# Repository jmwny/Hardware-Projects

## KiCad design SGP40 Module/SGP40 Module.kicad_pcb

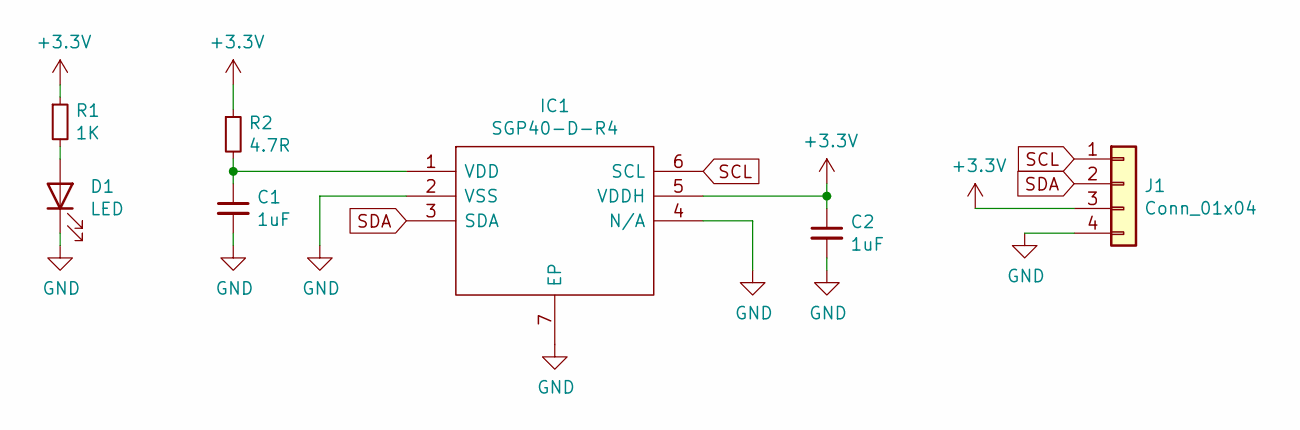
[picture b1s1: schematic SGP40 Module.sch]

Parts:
C1, C2: 1uF; C_0805_2012Metric
D1: LED; LED_0805_2012Metric
IC1: SGP40-D-R4; SON80P244X244X95-7N; Mouser Part Number 403-SGP40-D-R4
J1: Conn_01x04; PinHeader_1x04_P2.54mm_Vertical
R1: 1K; R_0805_2012Metric
R2: 4.7R; R_0805_2012Metric

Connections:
+3V3: C2.1, IC1.5 (VDDH), J1.3, R1.1, R2.1
GND: C1.2, C2.2, D1.1 (K), IC1.2 (VSS), IC1.4 (N/A), IC1.7 (EP), J1.4
unnamed: C1.1, IC1.1 (VDD), R2.2
unnamed: D1.2 (A), R1.2
SCL: IC1.6 (SCL), J1.1
SDA: IC1.3 (SDA), J1.2

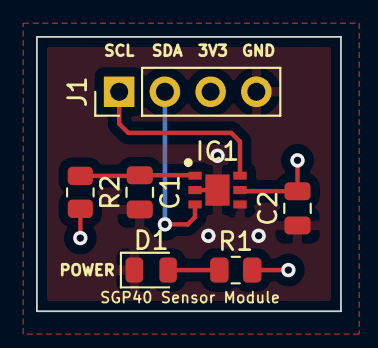
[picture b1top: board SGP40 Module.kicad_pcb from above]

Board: 4 copper layers, 16.9 x 15.2 mm, 7 parts (0 on the bottom side), 6 nets.

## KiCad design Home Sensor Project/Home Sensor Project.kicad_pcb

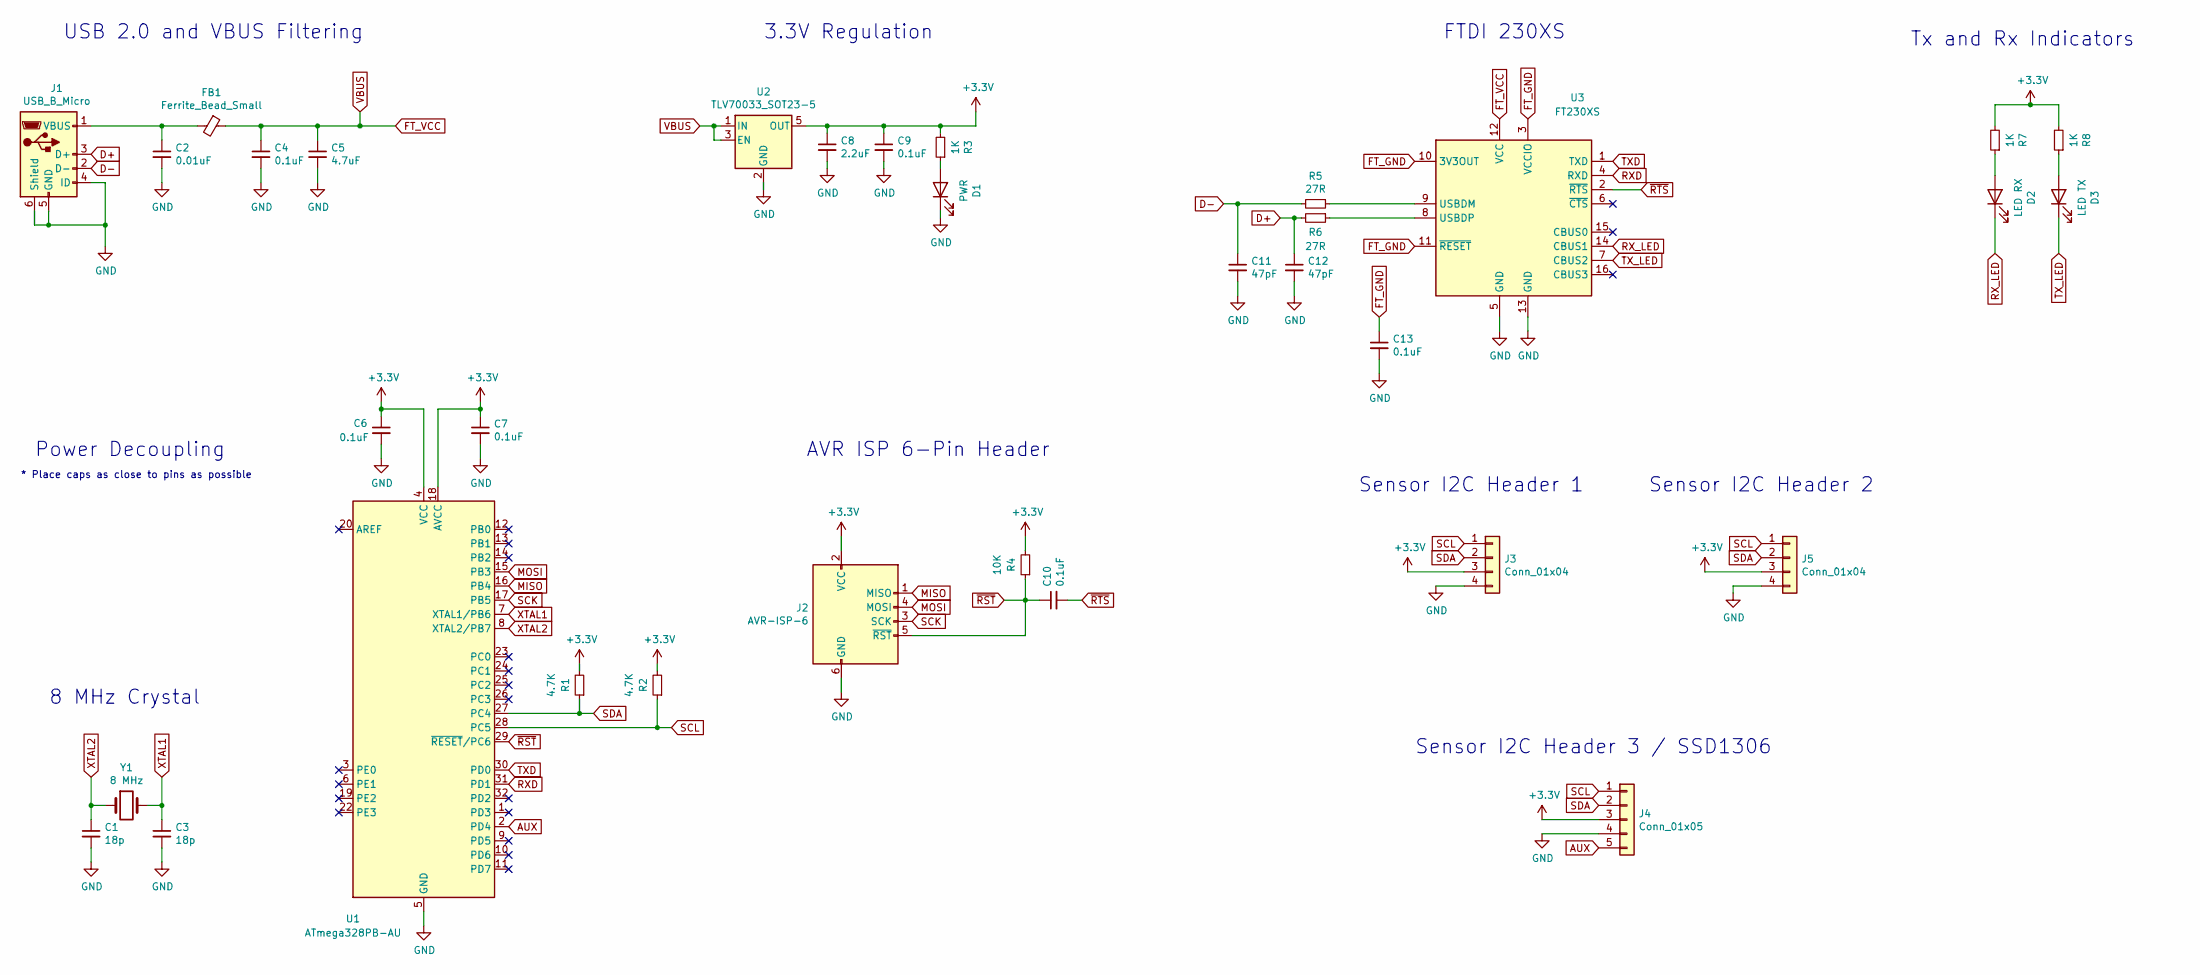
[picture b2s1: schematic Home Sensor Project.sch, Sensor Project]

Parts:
C1, C3: 18p; C_0805_2012Metric
C2: 0.01uF; C_0805_2012Metric
C4, C6, C7, C9, C10, C13: 0.1uF; C_0805_2012Metric
C5: 4.7uF; C_0805_2012Metric
C8: 2.2uF; C_0805_2012Metric
C11, C12: 47pF; C_0603_1608Metric
D1: PWR; LED_0805_2012Metric
D2: LED RX; LED_0805_2012Metric
D3: LED TX; LED_0805_2012Metric
FB1: Ferrite_Bead_Small; L_0805_2012Metric
J1: USB_B_Micro; USB_Micro-B_Amphenol_10118194_Horizontal
J2: AVR-ISP-6; PinHeader_2x03_P2.54mm_Vertical
J3, J5: Conn_01x04; PinHeader_1x04_P2.54mm_Vertical
J4: Conn_01x05; PinHeader_1x05_P2.54mm_Vertical
R1, R2: 4.7K; R_0805_2012Metric
R3, R7, R8: 1K; R_0805_2012Metric
R4: 10K; R_0805_2012Metric
R5, R6: 27R; R_0603_1608Metric
U1: ATmega328PB-AU; TQFP-32_7x7mm_P0.8mm
U2: TLV70033_SOT23-5; SOT-23-5
U3: FT230XS; SSOP-16_3.9x4.9mm_P0.635mm
Y1: 8 MHz; Crystal_SMD_Abracon_ABM7-2Pin_6.0x3.5mm

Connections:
+3V3: C6.1, C7.1, C8.1, C9.1, J2.2 (VCC), J3.3, J4.3, J5.3, R1.2, R2.2, R3.2, R4.2, R7.2, R8.2, U1.4 (VCC), U1.18 (AVCC), U2.5 (OUT)
AUX: J4.5, U1.2 (PD4)
D+: C12.1, J1.3 (D+), R6.2
D-: C11.1, J1.2 (D-), R5.2
FT_GND: C13.1, U3.3 (VCCIO), U3.10 (3V3OUT), U3.11 (~RESET)
FT_VCC: C4.1, C5.1, FB1.1, U2.1 (IN), U2.3 (EN), U3.12 (VCC)
GND: C1.2, C2.2, C3.2, C4.2, C5.2, C6.2, C7.2, C8.2, C9.2, C11.2, C12.2, C13.2, D1.1 (K), J1.4 (ID), J1.5 (GND), J1.6 (Shield), J2.6 (GND), J3.4, J4.4, J5.4, U1.5 (GND), U1.21 (GND), U2.2 (GND), U3.5 (GND), U3.13 (GND)
MISO: J2.1 (MISO), U1.16 (PB4)
MOSI: J2.4 (MOSI), U1.15 (PB3)
unnamed: C2.1, FB1.2, J1.1 (VBUS)
unnamed: D1.2 (A), R3.1
unnamed: D2.2 (A), R7.1
unnamed: D3.2 (A), R8.1
unnamed: R5.1, U3.9 (USBDM)
unnamed: R6.1, U3.8 (USBDP)
RXD: U1.31 (PD1), U3.4 (RXD)
RX_LED: D2.1 (K), U3.14 (CBUS1)
SCK: J2.3 (SCK), U1.17 (PB5)
SCL: J3.1, J4.1, J5.1, R2.1, U1.28 (PC5)
SDA: J3.2, J4.2, J5.2, R1.1, U1.27 (PC4)
TXD: U1.30 (PD0), U3.1 (TXD)
TX_LED: D3.1 (K), U3.7 (CBUS2)
XTAL1: C3.1, U1.7 (XTAL1/PB6), Y1.2
XTAL2: C1.1, U1.8 (XTAL2/PB7), Y1.1
~RST: C10.1, J2.5 (~RST), R4.1, U1.29 (~RESET~/PC6)
~RTS: C10.2, U3.2 (~RTS)

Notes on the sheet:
USB 2.0 and VBUS Filtering
Tx and Rx Indicators
FTDI 230XS
AVR ISP 6-Pin Header
Power Decoupling
8 MHz Crystal
* Place caps as close to pins as possible
Sensor I2C Header 1
3.3V Regulation
Sensor I2C Header 2
Sensor I2C Header 3 / SSD1306

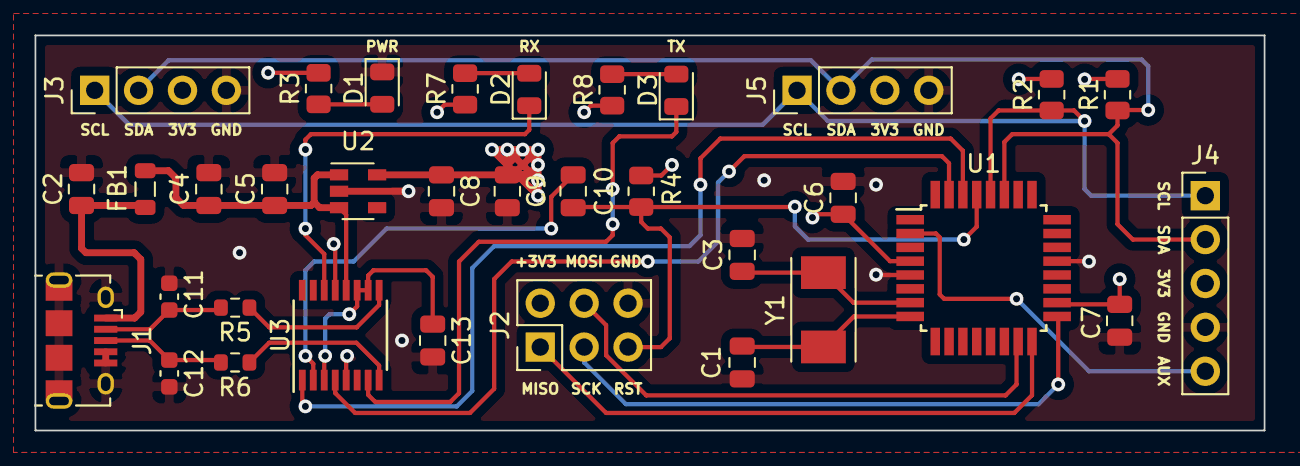
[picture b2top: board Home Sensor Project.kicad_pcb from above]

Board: 4 copper layers, 71.1 x 22.9 mm, 34 parts (0 on the bottom side), 26 nets.

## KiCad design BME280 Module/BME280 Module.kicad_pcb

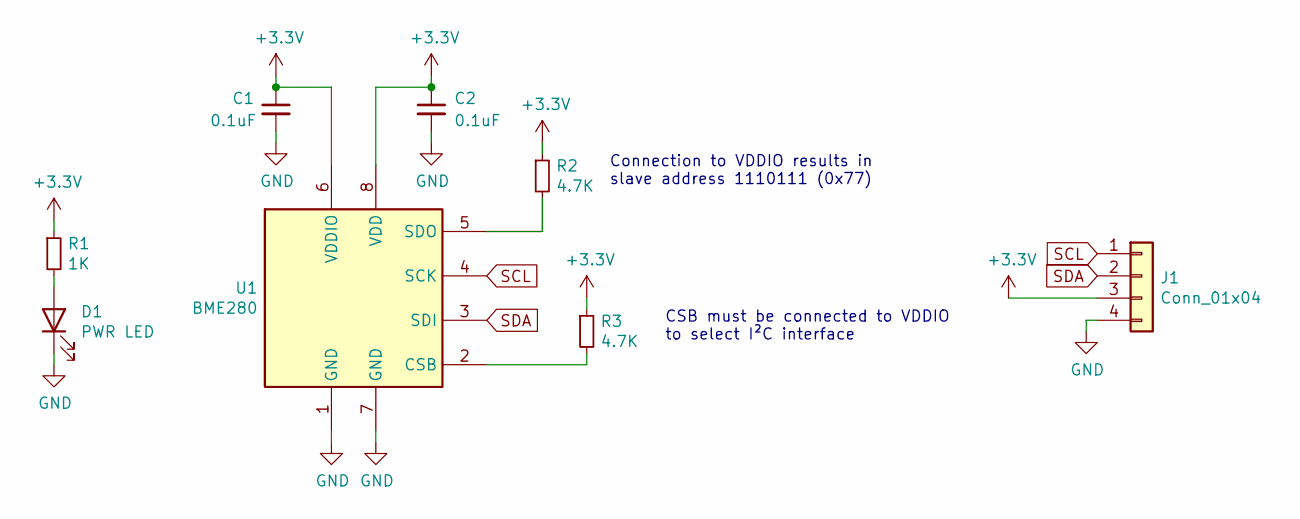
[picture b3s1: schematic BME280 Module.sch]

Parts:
C1, C2: 0.1uF; C_0805_2012Metric
D1: PWR LED; LED_0805_2012Metric
J1: Conn_01x04; PinHeader_1x04_P2.54mm_Vertical
R1: 1K; R_0805_2012Metric
R2, R3: 4.7K; R_0805_2012Metric
U1: BME280; Bosch_LGA-8_2.5x2.5mm_P0.65mm_ClockwisePinNumbering

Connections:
+3V3: C1.1, C2.1, J1.3, R1.1, R2.1, R3.1, U1.6 (VDDIO), U1.8 (VDD)
GND: C1.2, C2.2, D1.1 (K), J1.4, U1.1 (GND), U1.7 (GND)
unnamed: D1.2 (A), R1.2
unnamed: R2.2, U1.5 (SDO)
unnamed: R3.2, U1.2 (CSB)
SCL: J1.1, U1.4 (SCK)
SDA: J1.2, U1.3 (SDI)

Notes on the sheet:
CSB must be connected to VDDIO to select I²C interface
Connection to VDDIO results in slave address 1110111 (0x77)

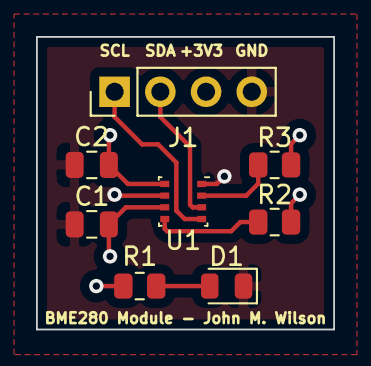
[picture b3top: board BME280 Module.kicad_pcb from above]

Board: 4 copper layers, 16.5 x 16.3 mm, 8 parts (0 on the bottom side), 7 nets.

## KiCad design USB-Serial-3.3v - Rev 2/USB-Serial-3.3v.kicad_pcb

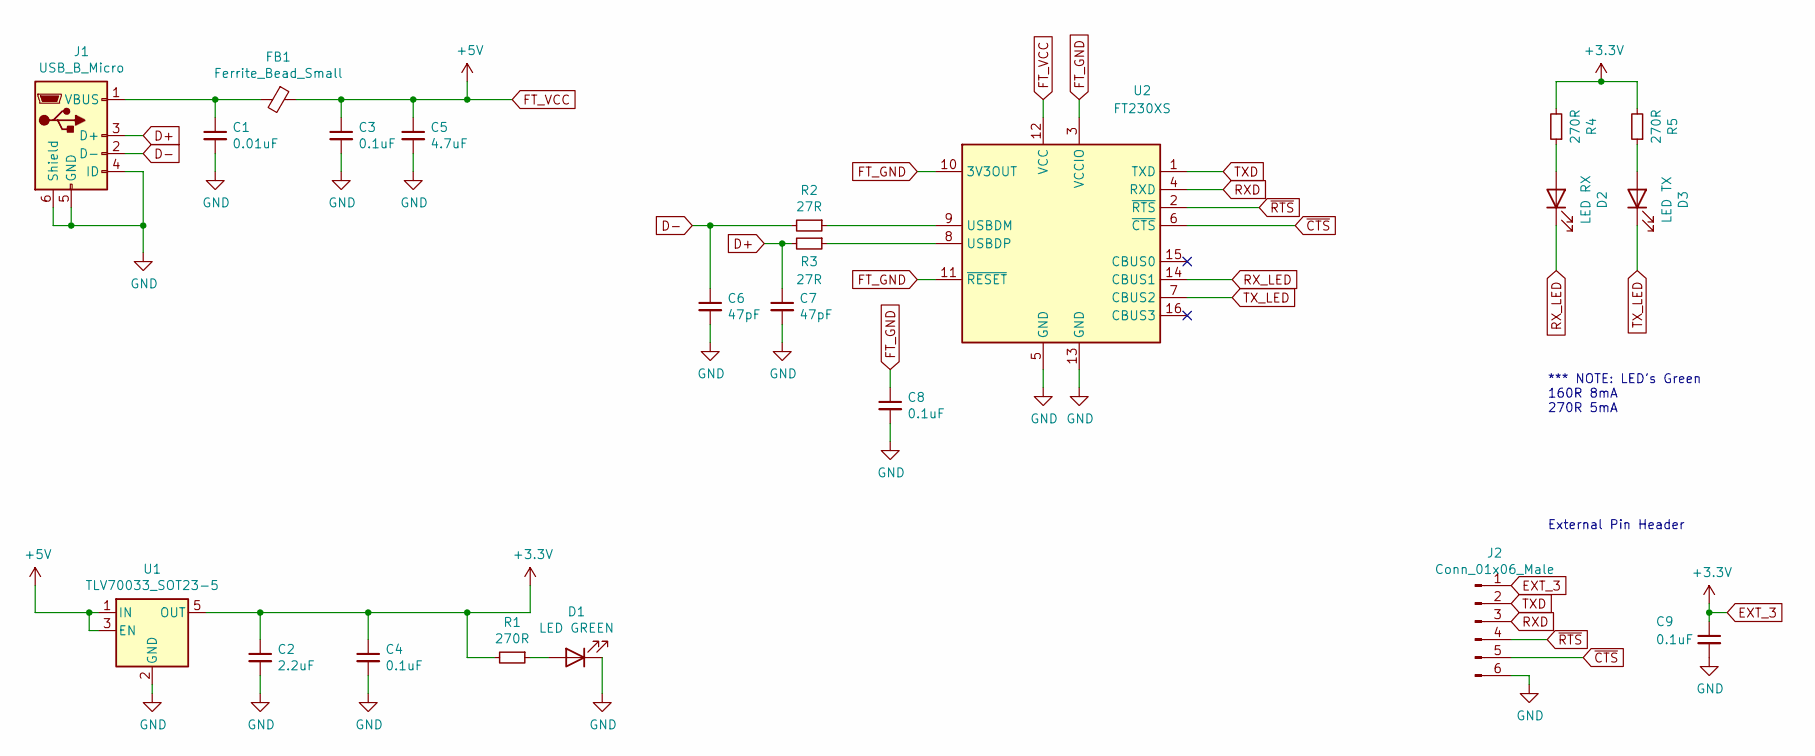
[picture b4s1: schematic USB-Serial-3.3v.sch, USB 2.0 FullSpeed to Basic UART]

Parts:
C1: 0.01uF; C_0805_2012Metric
C2: 2.2uF; C_0805_2012Metric
C3, C4, C8, C9: 0.1uF; C_0805_2012Metric
C5: 4.7uF; C_0805_2012Metric
C6, C7: 47pF; C_0603_1608Metric
D1: LED GREEN; LED_0805_2012Metric
D2: LED RX; LED_0805_2012Metric
D3: LED TX; LED_0805_2012Metric
FB1: Ferrite_Bead_Small; L_0805_2012Metric_Pad1.15x1.40mm_HandSolder
J1: USB_B_Micro; USB_Micro-B_Amphenol_10118194_Horizontal
J2: Conn_01x06_Male; PinHeader_1x06_P2.54mm_Vertical
R1, R4, R5: 270R; R_0805_2012Metric
R2, R3: 27R; R_0603_1608Metric
U1: TLV70033_SOT23-5; SOT-23-5
U2: FT230XS; SSOP-16_3.9x4.9mm_P0.635mm

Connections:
D+: C7.1, J1.3 (D+), R3.2
D-: C6.1, J1.2 (D-), R2.2
EXT_3: C2.1, C4.1, C9.1, J2.1, R1.2, R4.2, R5.2, U1.5 (OUT)
FT_GND: C8.1, U2.3 (VCCIO), U2.10 (3V3OUT), U2.11 (~RESET)
FT_VCC: C3.1, C5.1, FB1.1, U1.1 (IN), U1.3 (EN), U2.12 (VCC)
GND: C1.2, C2.2, C3.2, C4.2, C5.2, C6.2, C7.2, C8.2, C9.2, D1.1 (K), J1.4 (ID), J1.5 (GND), J1.6 (Shield), J2.6, U1.2 (GND), U2.5 (GND), U2.13 (GND)
unnamed: C1.1, FB1.2, J1.1 (VBUS)
unnamed: D1.2 (A), R1.1
unnamed: D2.2 (A), R4.1
unnamed: D3.2 (A), R5.1
unnamed: R2.1, U2.9 (USBDM)
unnamed: R3.1, U2.8 (USBDP)
RXD: J2.3, U2.4 (RXD)
RX_LED: D2.1 (K), U2.14 (CBUS1)
TXD: J2.2, U2.1 (TXD)
TX_LED: D3.1 (K), U2.7 (CBUS2)
~CTS: J2.5, U2.6 (~CTS)
~RTS: J2.4, U2.2 (~RTS)

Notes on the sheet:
External Pin Header
*** NOTE: LED's Green 160R 8mA 270R 5mA

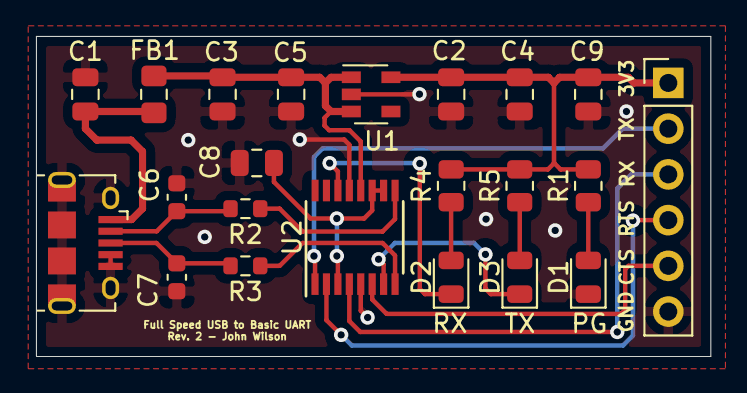
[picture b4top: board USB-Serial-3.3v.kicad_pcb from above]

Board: 2 copper layers, 37.5 x 17.8 mm, 22 parts (0 on the bottom side), 18 nets.

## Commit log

2021-01-28 Additions
2021-01-28 SGP40 Update
2021-01-28 Cleanup
2021-03-09 Audio Meter add and library additions
